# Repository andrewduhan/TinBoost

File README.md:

TinBoost
========

A simple holder for an OKR-T/6 bucking variable voltage converter, designed to fit in an Altoids-sized tin alongside two 18650 Lithium Ion batteries

Output adjustable from ~3.5V - 6V as is.   You can go as low as 1V output if you change the values of the 220 resistors.

The barrel jack is connected directly to battery + and -.  It is intended to allow easy in-circuit charging using an external Lithium-Ion charger appropriate for the battery (7.2V in the case of dual Li-Ion).  It could also be used as an unregulated output direct from the battery.  

**DO NOT CONNECT A STANDARD DC POWER SUPPLY TO THE DC JACK, YOU WILL DAMAGE YOUR BATTERY AND PROBABLY START A FIRE**

## BOM:
* OKR-T/6 (manually spread the pins to fit the board holes)
* C&K 1101 6A Switch (digikey # CKN5001)
* E-Switch illuminated right-angle tactile switch (digikey # EG4685-5)
* Bourns 3310Y 1k Pot (digikey # 3310Y-001-102L)
* 2x small through-hole tantalum 10uf caps
* 2x small 220ohm throughhole resistors ( for trim adjust )
* 1x small 6.8k throughhole resistor ( for EN pulldown )
* 1x small 1kohm throughhole resostor ( for tac switch LED )
* 1x standard through-hole DC barrel jack

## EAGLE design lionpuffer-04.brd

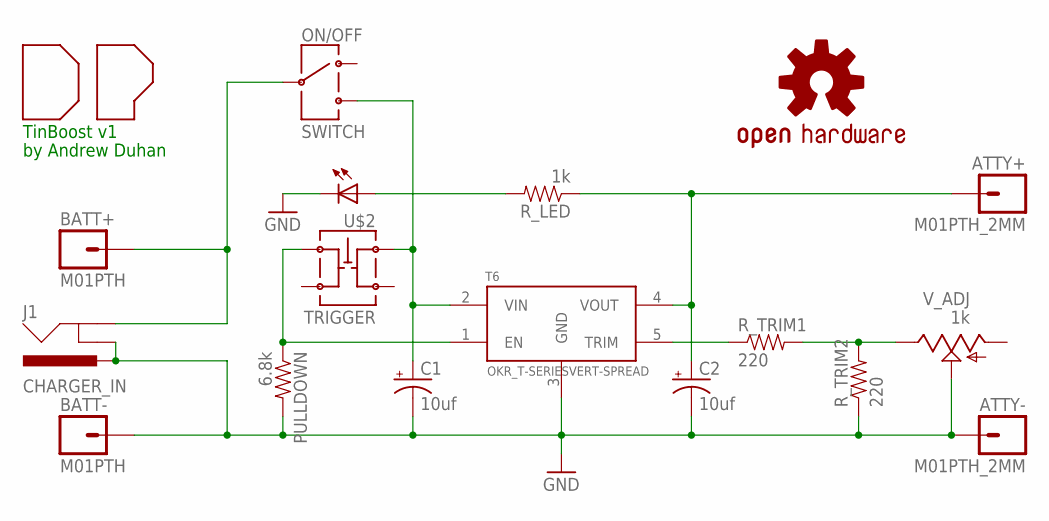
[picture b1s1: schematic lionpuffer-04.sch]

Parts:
ATTY+: M01PTH_2MM; 1X01_2MM
ATTY-: M01PTH_2MM; 1X01_2MM
BATT+: M01PTH; 1X01
BATT-: M01PTH; 1X01
C1, C2: 10uf; CPOL-RADIAL-10UF-25V
J1: CHARGER_IN; POWER_JACK_PTH
ON/OFF: SWITCH; SWITCH-CK1101
PULLDOWN: 6.8k; 1/6W-RES
R_LED: 1k; 1/6W-RES
R_TRIM1, R_TRIM2: 220; 1/6W-RES
T6: OKR_T-SERIESVERT-SPREAD; OKR-T/6_10-VERT-SPACED
U$1: OSHW-LOGOM; OSHW-LOGO-M
U$2: TRIGGER; E-SWITCH_TL1250
U$3: DP_LOGO
V_ADJ: 1k; POT-TOP-BOURNS

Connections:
ATTY+: ATTY+.1, C2.1 (+), R_LED.1, T6.4 (VOUT)
BATT+: BATT+.1, J1.GND, ON/OFF.2
GND: ATTY-.1, BATT-.1, C1.2 (-), C2.2 (-), J1.GNDBREAK, J1.PWR, PULLDOWN.2, R_TRIM2.1, T6.3 (GND), U$2.5 (C), V_ADJ.2 (W)
unnamed: R_TRIM1.2, R_TRIM2.2, V_ADJ.3 (B)
unnamed: PULLDOWN.1, T6.1 (EN), U$2.3
unnamed: R_TRIM1.1, T6.5 (TRIM)
unnamed: R_LED.2, U$2.6 (A)
VIN: C1.1 (+), ON/OFF.3, T6.2 (VIN), U$2.1

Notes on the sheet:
TinBoost v1
by Andrew Duhan

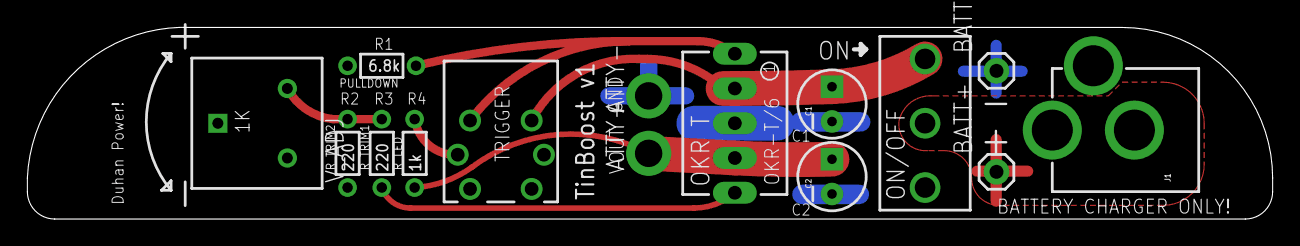
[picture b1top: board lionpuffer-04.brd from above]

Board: 2 copper layers, 91.0 x 14.0 mm, 17 parts (1 on the bottom side), 8 nets.

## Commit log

2012-05-30 version 1
2012-05-30 layout pic for readme
2012-05-30 readme typo

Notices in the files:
parts and their libraries:
SparkFun: Licensing: CC v3.0 Share-Alike You are welcome to use this library for commercial purposes.
